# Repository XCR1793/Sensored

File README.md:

# Sensored
A simple very dense sensor module which includes an IMU and an environmental sensor. The system is designed to be easily integrated with any other projects and is relatively cheap to fabricate.

## Features
* IMU: ICM20948 (3 Axis Accelerometer + 3 Axis Gyroscope + 3 Axis Magnetometer)
* ENV: BME280 (Temperature + Humidity + Pressure)
* I2C: Internally Pulled Up 10K
* LDO: 3V3 input power is stepped down to 1.8v for other IC functions

## [Embedded](/Embedded/README.md)
The Sensored board integrates two key devices: the ICM20948, a 9-axis motion sensor, and the BME280 for environmental monitoring. Designed for direct integration onto host boards, it operates on 3.3 V with onboard regulation for the IMU, providing a compact foundation for motion and environmental sensing in embedded systems.

## Roadmap
* Milestones: Fabricating V1.0
* Milestones: Confirmed V1.0 circuit design
* Milestones: Fabricating V2.0
* Milestones: Confirmed V2.0 circuit design

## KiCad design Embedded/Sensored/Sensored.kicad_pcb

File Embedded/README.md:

# Sensored - Embedded
There are 2 sensors on the Sensored board, these are the ICM20948 and the BME280. The ICM20948 is a compact IMU with 3 axis accelerometer, gyroscope and magnetometer. The BME is a sensitive sensor that measures temperature, pressure and humidity. The I2C lanes are pulled up to 3V3 via 10K resistors. There is also a 1V8 LDO for converting 3V3 to 1V8 as the ICM20948 requires it for its internal VDDIO pin. DO NOT EXCEED 3V3 on the 3V3, SDA and SCL pins, this device also DOES NOT HAVE reverse voltage protection as it doesnt require one. The board is designed to be soldered directly onto other boards and is not ment to be an externally mounted module. You can do this by removing the middle "Island" from the outer ring.

Here are the specifications for the ICM-20948 and BME280 sensors.

## ICM-20948
| Sensor        | Axis     | Full-Scale Range                 | Sensitivity                 
| ------------- | -------- | -------------------------------- | ----------------------------
| Accelerometer | X, Y, Z  | ±2g, ±4g, ±8g, ±16g              | 16384, 8192, 4096, 2048 LSB/g
| Gyroscope     | X, Y, Z  | ±250, ±500, ±1000, ±2000 °/s     | 131, 65.5, 32.8, 16.4 LSB/°/s
| Magnetometer  | X, Y, Z  | ±4900 µT                         | 0.15 µT/LSB

## BME280
| Sensor      | Parameter   | Measurement Range   | Resolution
| ----------- | ----------- | ------------------- | -----------
| Pressure    | Pressure    | 300 to 1100 hPa     | 0.18 Pa
| Temperature | Temperature | -40 to 85 °C        | 0.01 °C
| Humidity    | Humidity    | 0 to 100 %RH        | 0.008 %RH

---

The entire board was routed on one side with a single ground plate to reduce EMI. The inner island is 8mm x 8mm which is a very small footprint and should fit in nearly any project. The fabricated board is using a 0.8mm board thickness rather than the standard 1.6mm as this also reduces the overall 3D footprint. All of the LCSC BOM part numbers are included within the KiCAD file and can be directly converted to Gerber + drill + placement files and sent off to JLCPCB to be manufactured (JLCPCB was used as they are cheap). The cost is roughly $150 AUD for 5 fully assembled boards therefore its ~$30 / Board.

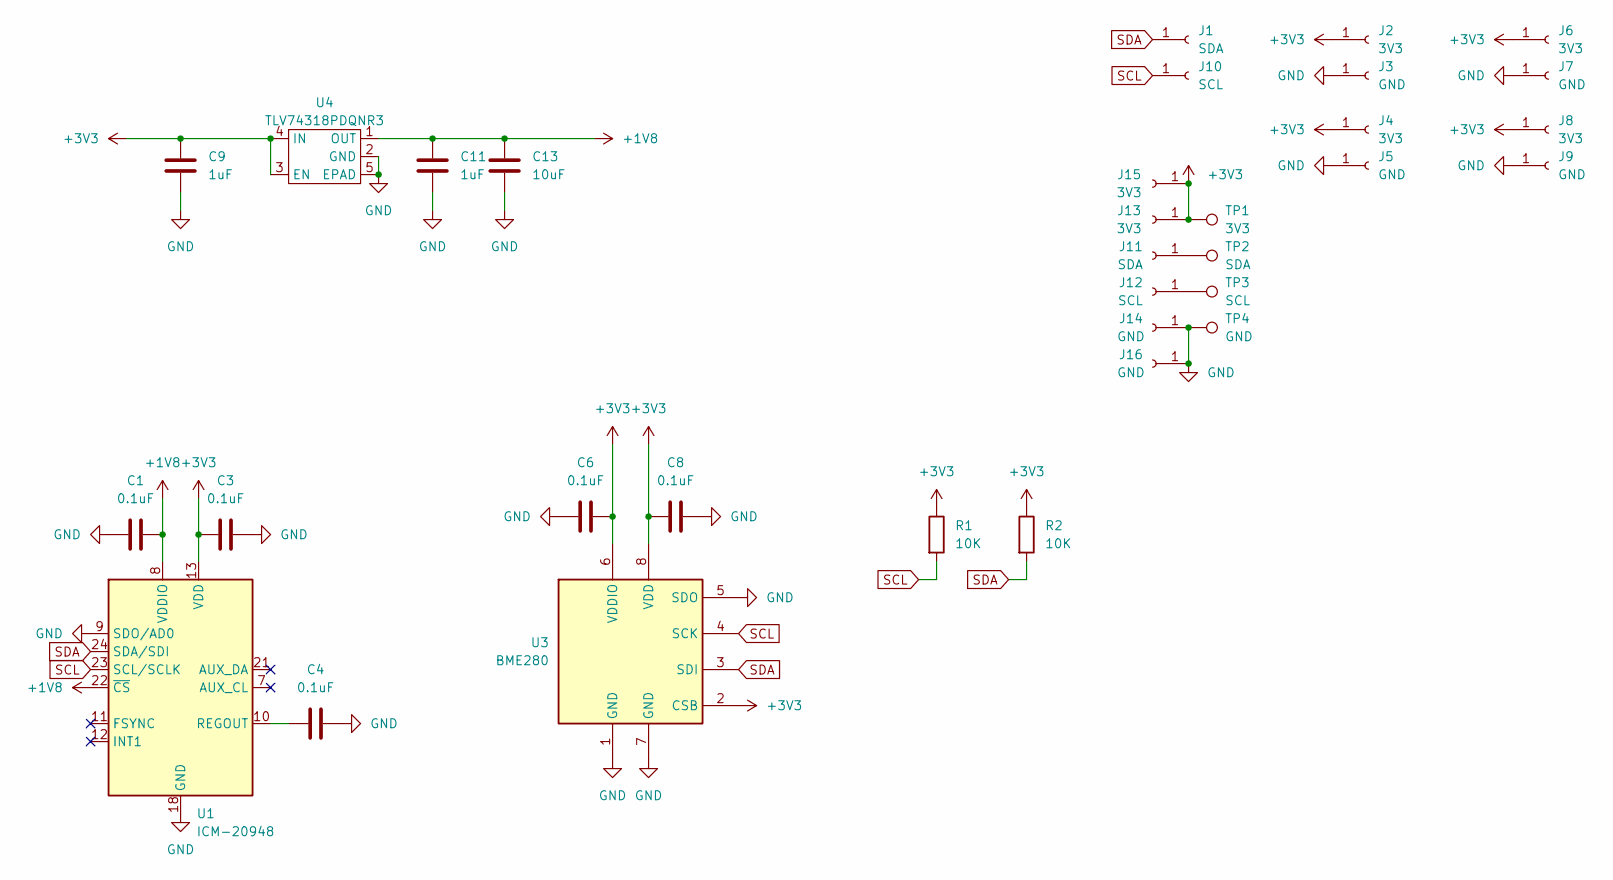
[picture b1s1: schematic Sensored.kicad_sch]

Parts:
C1, C3, C4, C6, C8: 0.1uF; C_0402_1005Metric; LCSC C1525
C9, C11: 1uF; R_0402_1005Metric; LCSC C52923
C13: 10uF; C_0402_1005Metric; LCSC C15525
J1, J11: SDA; 1mm Pads
J2, J4, J6, J8, J13, J15: 3V3; 1mm Pads
J3, J5, J7, J9, J14, J16: GND; 1mm Pads
J10, J12: SCL; 1mm Pads
R1, R2: 10K; R_0402_1005Metric; LCSC C25744
TP1: 3V3; PinHeader_1x01_P2.54mm_Vertical
TP2: SDA; PinHeader_1x01_P2.54mm_Vertical
TP3: SCL; PinHeader_1x01_P2.54mm_Vertical
TP4: GND; PinHeader_1x01_P2.54mm_Vertical
U1: ICM-20948; InvenSense_QFN-24_3x3mm_P0.4mm; LCSC C726001
U3: BME280; Bosch_LGA-8_2.5x2.5mm_P0.65mm_ClockwisePinNumbering; LCSC C92489
U4: TLV74318PDQNR3; UDFN-4-1EP_1x1mm_P0.65mm_EP0.48x0.48mm; LCSC C2860843

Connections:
+1V8: C1.2, C11.1, C13.1, U1.8 (VDDIO), U1.22 (~CS), U4.1 (OUT)
+3V3: C3.1, C6.2, C8.1, C9.1, J2.1, J4.1, J6.1, J8.1, J13.1, J15.1, R1.1, R2.1, TP1.1, U1.13 (VDD), U3.2 (CSB), U3.6 (VDDIO), U3.8 (VDD), U4.3 (EN), U4.4 (IN)
GND: C1.1, C3.2, C4.2, C6.1, C8.2, C9.2, C11.2, C13.2, J3.1, J5.1, J7.1, J9.1, J14.1, J16.1, TP4.1, U1.9 (SDO/AD0), U1.18 (GND), U1.20 (GND), U3.1 (GND), U3.5 (SDO), U3.7 (GND), U4.2 (GND), U4.5 (EPAD)
unnamed: J11.1, TP2.1
unnamed: J12.1, TP3.1
unnamed: C4.1, U1.10 (REGOUT)
SCL: J10.1, R1.2, U1.23 (SCL/SCLK), U3.4 (SCK)
SDA: J1.1, R2.2, U1.24 (SDA/SDI), U3.3 (SDI)

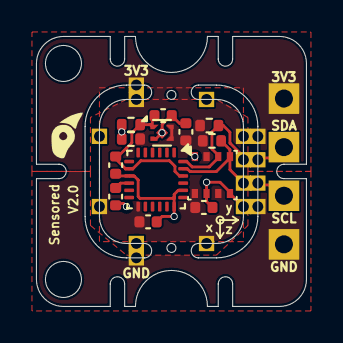
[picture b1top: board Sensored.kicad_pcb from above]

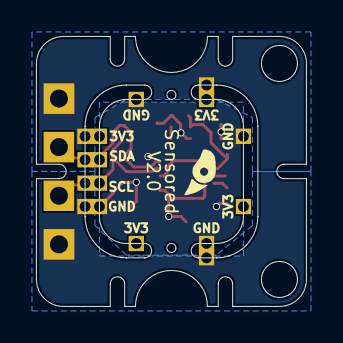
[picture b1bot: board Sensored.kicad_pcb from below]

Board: 2 copper layers, 15.0 x 15.0 mm, 33 parts (10 on the bottom side), 8 nets.

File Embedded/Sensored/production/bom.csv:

Designator,Footprint,Quantity,Value,LCSC Part #
"C1, C3, C4, C6, C8",0402,5,0.1uF,C1525
"C11, C9",0402,2,1uF,C52923
C13,0402,1,10uF,C15525
"J1, J11",1mm Pads,2,SDA,
"J10, J12",1mm Pads,2,SCL,
"J13, J15, J2, J4, J6, J8",1mm Pads,6,3V3,
"J14, J16, J3, J5, J7, J9",1mm Pads,6,GND,
"R1, R2",0402,2,10K,C25744
TP1,PinHeader_1x01_P2.54mm_Vertical,1,3V3,
TP2,PinHeader_1x01_P2.54mm_Vertical,1,SDA,
TP3,PinHeader_1x01_P2.54mm_Vertical,1,SCL,
TP4,PinHeader_1x01_P2.54mm_Vertical,1,GND,
U1,InvenSense_QFN-24_3x3mm_P0.4mm,1,ICM-20948,C726001
U3,Bosch_LGA-8_2.5x2.5mm_P0.65mm_ClockwisePinNumbering,1,BME280,C92489
U4,UDFN-4-1EP_1x1mm_P0.65mm_EP0.48x0.48mm,1,TLV74318PDQNR3,C2860843

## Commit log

2024-12-20 Added Some Ideation
2024-12-21 Added Castellated Pins & Removed Micro SD Card
2024-12-21 Added Stabiliser GND Pins & Finished Routing
2024-12-21 Added Markings & Component Adjustment
2024-12-21 Added CAD Model
2024-12-21 Replaced Side GND Pins with GND EPad
2024-12-21 Updated CAD Origin & Materials
2024-12-22 Generated BOM, JLCPCB Assembly Parts, Production Files, Drill Positions
2024-12-22 Added Pick & Place Component Position Files
2024-12-23 Optimised JLCPCB Specific Parts
2024-12-25 Added Initial Documentation
2025-05-16 Removed Obsolete Files
2025-05-16 Added System Connection Diagram, Layout Guide & Replacement PCB Design Ideation
2025-05-17 Modified Outline & Component Placements for V2
2025-05-17 Modified Component Placement & Added Adapting Pads
2025-05-17 Added Component Routing
2025-05-18 Added Usage Example
2025-05-18 Added V1.0 Archive
2025-05-19 Added Orientation Marker
2025-05-19 Verified LCSC Components
2025-05-20 Modified Layout for JLCPCB
2025-05-21 Modified Board Edge Slots to be shorter
2025-05-23 Modified Board Edge to 0.8mm Tolerance
2025-05-23 Modified the Pin Positions
2025-05-25 Modified Via Positions to prevent potential component floating
2025-06-01 Modified README Roadmap and Features List
2025-06-14 Added Project Image
2025-06-14 Modified README Roadmap
2025-06-14 Modified README to fix image directory
2025-09-02 Removed Software section as it is no longer needed
    Sensor driving instructions and register maps are available in the ICM20948 and BME280 datasheets.
2025-09-02 Modified README milestones and added embedded brief
2025-09-02 Added Embedded specifications along with description
